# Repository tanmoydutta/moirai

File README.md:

# Moirai
This is an STM32WLE5 standalone module built with Seeed Studio Wio-E5. The objective was to replace the proprietary firmware and make use of the STM32 chip to run a custom firmware which makes use of the built in SubGHz radio for specific purposes. At the back of the PCB there are interface touch pads for Software Debug interface as well as an UART debug connector pads. This module is pin compatible with ESP02S modules and ESP8685-WROOM-03 this helps to add SubGHz and LoRaWAN cpability (with proper firmware) to any existing solution built for limited WiFi and Bluetooth solutions.

This is a size comparison of the built module. Note that in this picture the pinout is mirrored but the actual design is done the other way.

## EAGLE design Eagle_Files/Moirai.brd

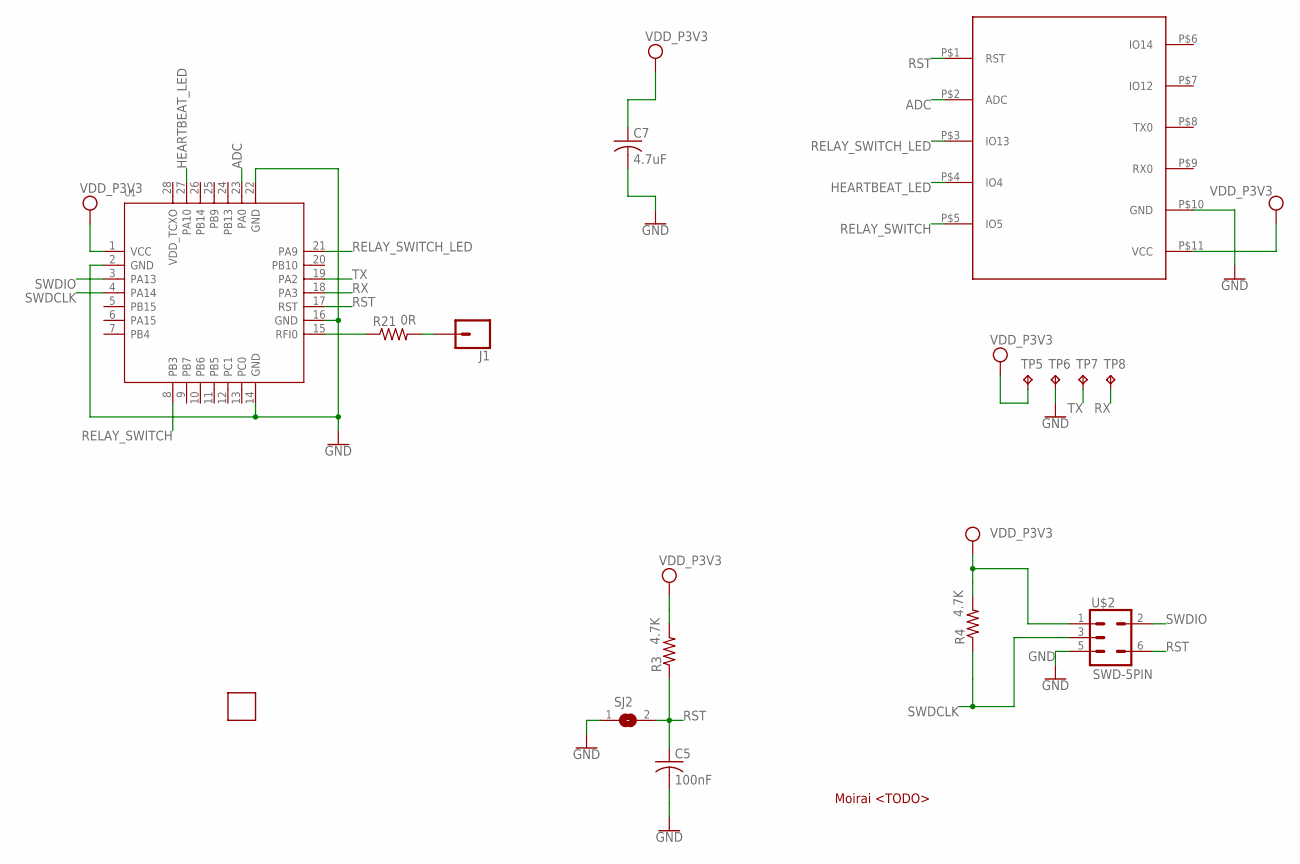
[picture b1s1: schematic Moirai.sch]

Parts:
C5: 100nF; C0402
C7: 4.7uF; C0402
J1: CONN_01; 1X01
R3, R4: 4.7K; R0402
R21: 0R; R0402
SJ2: SJ
TP5, TP6, TP7, TP8: TPB1,27; B1,27
U1: MODULE_LORA_E5; MODULE28P-1.25-12X12X2.5MM
U$1: ESP02SESP02S_MIRROR; ESP02S_MIRROR
U$2: SWD-5PIN; PAD_05_03X2_TP_NO4
U$3: SMARTT_SMALL

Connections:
ADC: U1.23 (PA0), U$1.P$2 (ADC)
GND: C5.2, C7.2, SJ2.1, TP6.TP, U1.2 (GND), U1.14 (GND), U1.16 (GND), U1.22 (GND), U$1.P$10 (GND), U$2.5
HEARTBEAT_LED: U1.27 (PA10), U$1.P$4 (IO4)
unnamed: R21.1, U1.15 (RFI0)
unnamed: J1.1, R21.2
RELAY_SWITCH: U1.8 (PB3), U$1.P$5 (IO5)
RELAY_SWITCH_LED: U1.21 (PA9), U$1.P$3 (IO13)
RST: C5.1, R3.1, SJ2.2, U1.17 (RST), U$1.P$1 (RST), U$2.6
RX: TP8.TP, U1.18 (PA3)
SWDCLK: R4.1, U1.4 (PA14), U$2.3
SWDIO: U1.3 (PA13), U$2.2
TX: TP7.TP, U1.19 (PA2)
VCC: C7.1, R3.2, R4.2, TP5.TP, U1.1 (VCC), U$1.P$11 (VCC), U$2.1

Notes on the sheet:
Moirai <TODO>

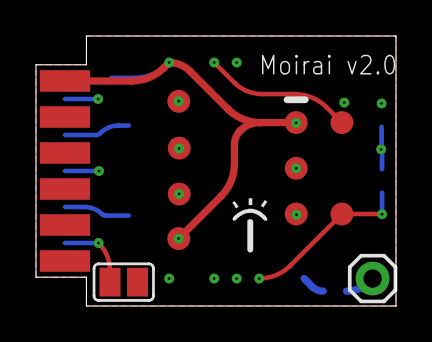
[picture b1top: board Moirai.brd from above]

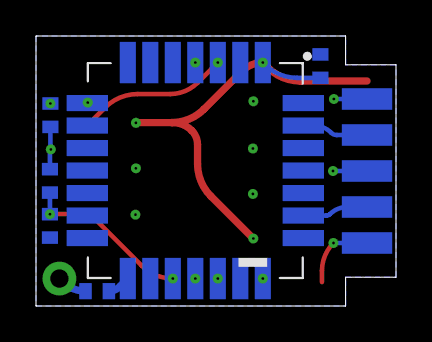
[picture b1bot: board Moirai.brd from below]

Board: 6 copper layers, 20.0 x 15.0 mm, 15 parts (7 on the bottom side), 13 nets.

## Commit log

2026-05-05 Adding files to new repository
2026-05-05 Updating Read Me to add image links
2026-05-14 Adding doc
2026-05-14 Adding doc and images
2026-05-14 Adding images
2026-05-14 Updating doc for broken image URL
2026-05-14 Updating doc

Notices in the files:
parts and their libraries:
SparkFun-Connectors: Licensing: Creative Commons ShareAlike 4.0 International - https://creativecommons.org/licenses/by-sa/4.0
